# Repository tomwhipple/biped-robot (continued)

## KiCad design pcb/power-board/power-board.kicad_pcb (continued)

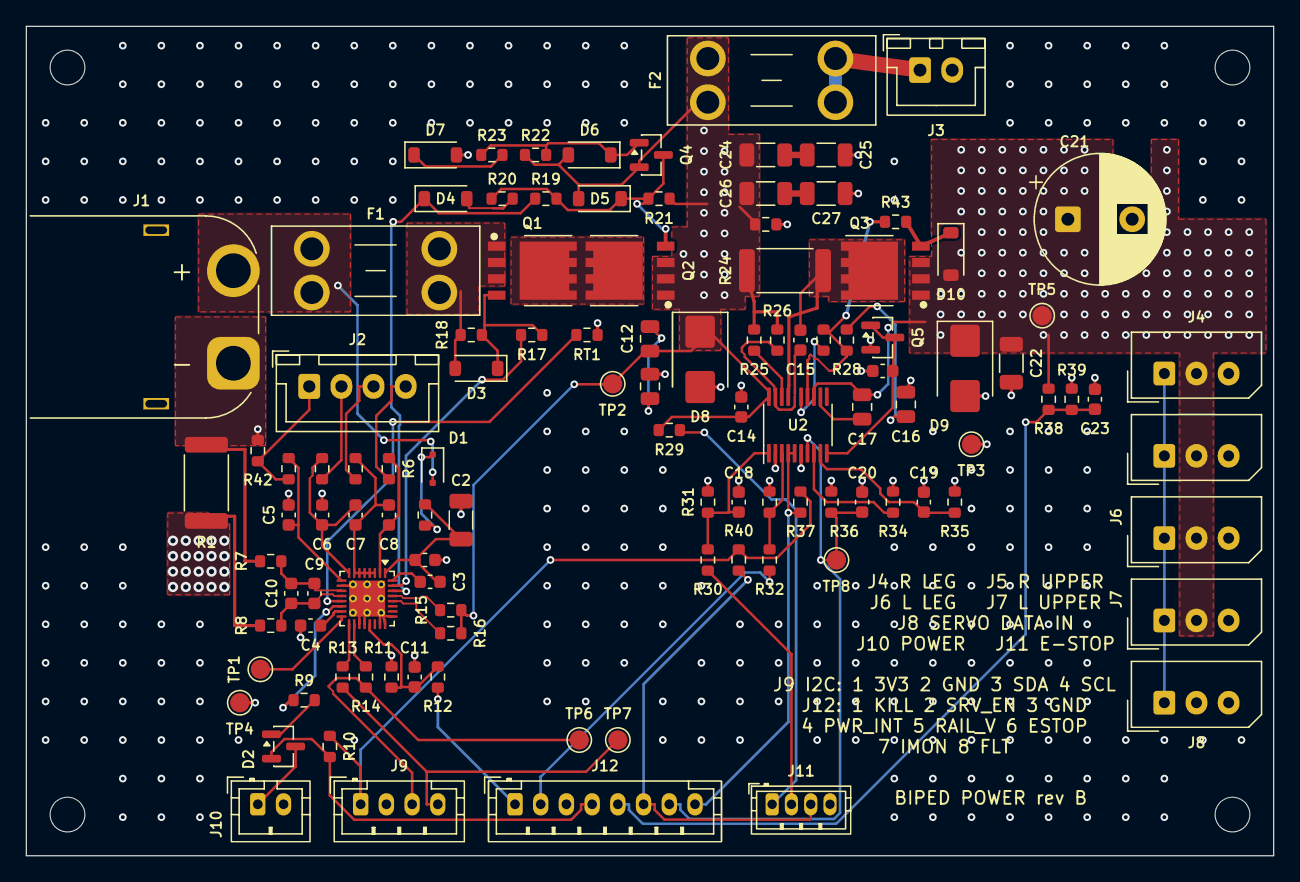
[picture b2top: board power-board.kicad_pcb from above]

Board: 4 copper layers, 97.0 x 64.5 mm, 115 parts (0 on the bottom side), 68 nets.

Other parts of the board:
H1, H2, H3, H4: M2.5; MountingHole_2.7mm_M2.5

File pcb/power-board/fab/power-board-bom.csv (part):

"Refs","Value","Footprint","MPN","Datasheet","Qty"
"C1","100p 50V","Capacitor_SMD:C_0603_1608Metric","Yageo CC0603JRNPO9BN101","https://yageogroup.com/download/specsheet/CC0603JRNPO9BN101","1"
"C2","2.2u 50V","Capacitor_SMD:C_1206_3216Metric","KEMET C1206C225K5RACTU","https://content.kemet.com/datasheets/KEM_C1002_X7R_SMD.pdf","1"
"C3","470n 25V","Capacitor_SMD:C_0603_1608Metric","Yageo CC0603KRX7R8BB474","https://yageogroup.com/content/datasheet/asset/file/UPY-GPHC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","1"
"C4","2.2u 10V","Capacitor_SMD:C_0603_1608Metric","Yageo CC0603KRX7R6BB225","https://yageogroup.com/content/datasheet/asset/file/UPY-GPHC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","1"
"C5-C8","100n 25V","Capacitor_SMD:C_0603_1608Metric","Yageo CC0603KRX7R9BB104","https://yageogroup.com/content/datasheet/asset/file/UPY-GPHC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","4"
"C9,C23","100n","Capacitor_SMD:C_0603_1608Metric","Yageo CC0603KRX7R9BB104","https://yageogroup.com/content/datasheet/asset/file/UPY-GPHC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","2"
"C10","100p","Capacitor_SMD:C_0603_1608Metric","Yageo CC0603JRNPO9BN101","https://yageogroup.com/download/specsheet/CC0603JRNPO9BN101","1"
"C11,C18,C20","10n","Capacitor_SMD:C_0603_1608Metric","Yageo CC0603KRX7R9BB103","https://yageogroup.com/content/datasheet/asset/file/UPY-GPHC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","3"
"C12,C13","100n 50V","Capacitor_SMD:C_0805_2012Metric","Yageo CC0805KRX7R9BB104","https://yageogroup.com/content/datasheet/asset/file/UPY-GPHC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","2"
"C14","100n 50V","Capacitor_SMD:C_0603_1608Metric","Yageo CC0603KRX7R9BB104","https://yageogroup.com/content/datasheet/asset/file/UPY-GPHC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","1"
"C15","1n","Capacitor_SMD:C_0603_1608Metric","Yageo CC0603JRNPO9BN102","https://yageogroup.com/download/specsheet/CC0603JRNPO9BN101","1"
"C16","330n 50V","Capacitor_SMD:C_0805_2012Metric","Samsung CL21B334KBFNNNE","https://product.samsungsem.com/mlcc/CL21B334KBFNNN.do","1"
"C17","4.7u 25V","Capacitor_SMD:C_0805_2012Metric","Samsung CL21B475KAFNNNE","https://product.samsungsem.com/mlcc/CL21B334KBFNNN.do","1"
"C19","680n 16V","Capacitor_SMD:C_0603_1608Metric","Yageo CC0603KRX7R7BB684","https://yageogroup.com/content/datasheet/asset/file/UPY-GPHC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","1"
"C21","1000u 25V","Capacitor_THT:CP_Radial_D10.0mm_P5.00mm","Panasonic EEU-FR1E102","https://industrial.panasonic.com/cdbs/www-data/pdf/RDF0000/A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","1"
"C22","10u 25V","Capacitor_SMD:C_1206_3216Metric","Samsung CL31B106KLHNNNE","https://mm.digikey.com/Volume0/opasdata/d220001/medias/docus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","1"
"D1","PMEG4002EJ","Diode_SMD:D_SOD-323F","Nexperia PMEG4002EJ-QX","https://assets.nexperia.com/documents/data-sheet/PMEG4002EJ-Q.pdf","1"
"D2","BAT54C","Package_TO_SOT_SMD:SOT-23","Diotec BAT54C","https://diotec.com/request/datasheet/bat54.pdf","1"
"D3,D5,D6","16V","Diode_SMD:D_SOD-123","Diodes MMSZ5246B-7-F","https://www.diodes.com/assets/Datasheets/ds18010.pdf","3"
"D4,D7","1N4148W","Diode_SMD:D_SOD-123","Diodes 1N4148W-7-F","https://www.diodes.com/assets/Datasheets/BAV16W_1N4148W.pdf","2"
"D8,D9","SMBJ15A","Diode_SMD:D_SMB","Bourns SMBJ15A","https://www.bourns.com/docs/Product-Datasheets/SMBJ.pdf","2"
"F1","15A","Fuse:Fuseholder_Blade_Mini_Keystone_3568","Keystone 3568 + Littelfuse 0297015.WXNV","https://www.keyelco.com/userAssets/file/K75p48.pdf","1"
"F2","3A","Fuse:Fuseholder_Blade_Mini_Keystone_3568","Keystone 3568 + Littelfuse 0297003.WXNV","https://www.keyelco.com/userAssets/file/K75p48.pdf","1"
"J1","XT60 pack","power-board:AMASS_XT60PW-M_1x02_P7.20mm_Horizontal_EdgeMount","Amass XT60PW-M","https://www.china-amass.com","1"
"J2","Balance 3S","Connector_JST:JST_XH_B4B-XH-A_1x04_P2.50mm_Vertical","JST B4B-XH-A","https://www.jst-mfg.com/product/pdf/eng/eXH.pdf","1"
"J3","LOGIC OUT","Connector_JST:JST_XH_B2B-XH-A_1x02_P2.50mm_Vertical","JST B2B-XH-A","https://www.jst-mfg.com/product/pdf/eng/eXH.pdf","1"
"J4","Servo R leg","Connector_Molex:Molex_SPOX_5267-03A_1x03_P2.50mm_Vertical","Molex 22-03-5035","https://www.molex.com/en-us/products/part-detail/22035035","1"
"J5","Servo R upper","Connector_Molex:Molex_SPOX_5267-03A_1x03_P2.50mm_Vertical","Molex 22-03-5035","https://www.molex.com/en-us/products/part-detail/22035035","1"
"J6","Servo L leg","Connector_Molex:Molex_SPOX_5267-03A_1x03_P2.50mm_Vertical","Molex 22-03-5035","https://www.molex.com/en-us/products/part-detail/22035035","1"
"J7","Servo L upper","Connector_Molex:Molex_SPOX_5267-03A_1x03_P2.50mm_Vertical","Molex 22-03-5035","https://www.molex.com/en-us/products/part-detail/22035035","1"
"J8","Data from H5","Connector_Molex:Molex_SPOX_5267-03A_1x03_P2.50mm_Vertical","Molex 22-03-5035","https://www.molex.com/en-us/products/part-detail/22035035","1"
"J9","I2C (to P1)","Connector_JST:JST_PH_B4B-PH-K_1x04_P2.00mm_Vertical","JST B4B-PH-K-S","https://www.jst-mfg.com/product/pdf/eng/ePH.pdf","1"
"J10","POWER button","Connector_JST:JST_PH_B2B-PH-K_1x02_P2.00mm_Vertical","JST B2B-PH-K-S","https://www.jst-mfg.com/product/pdf/eng/ePH.pdf","1"
"J11","E-STOP button","Connector_JST:JST_PH_B4B-PH-K_1x04_P2.00mm_Vertical","JST B4B-PH-K-S","https://www.jst-mfg.com/product/pdf/eng/ePH.pdf","1"
"J12","Control (ESP32)","Connector_JST:JST_PH_B8B-PH-K_1x08_P2.00mm_Vertical","JST B8B-PH-K-S","https://www.jst-mfg.com/product/pdf/eng/ePH.pdf","1"
"Q1-Q3","CSD17556Q5B","power-board:TI_SON-8_5x6mm_P1.27mm_CSD17556Q5B","CSD17556Q5B","https://www.ti.com/lit/ds/symlink/csd17556q5b.pdf","3"
"Q4","2N7002","Package_TO_SOT_SMD:SOT-23","Vishay 2N7002K-T1-GE3","https://www.vishay.com/docs/71333/2n7002k.pdf","1"
"Q5","MMBT3904","Package_TO_SOT_SMD:SOT-23","Diodes MMBT3904-7-F","https://www.diodes.com/assets/Datasheets/MMBT3904.pdf","1"
"R1","1m","Resistor_SMD:R_2512_6332Metric","Bourns CSS2H-2512R-1L00FE","https://www.bourns.com/docs/product-datasheets/css2h-2512.pdf","1"
"R2,R7,R8,R13,R14,R25","100","Resistor_SMD:R_0603_1608Metric","Yageo RC0603FR-07100RL","https://yageogroup.com/content/datasheet/asset/file/PYU-RC_G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","6"
"R3-R6","20","Resistor_SMD:R_0603_1608Metric","Yageo RC0603FR-0720RL","https://yageogroup.com/content/datasheet/asset/file/PYU-RC_G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","4"
"R9-R11,R15,R16,R19,R23,R37,R39,R40","10k","Resistor_SMD:R_0603_1608Metric","Yageo RC0603FR-0710KL","https://yageogroup.com/content/datasheet/asset/file/PYU-RC_G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","10"
"R12,R29,R32","1k","Resistor_SMD:R_0603_1608Metric","Yageo RC0603FR-071KL","https://yageogroup.com/content/datasheet/asset/file/PYU-RC_G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","3"
"R17","5.1k","Resistor_SMD:R_0603_1608Metric","Vishay CRCW06035K10FKEA","https://www.vishay.com/docs/20035/dcrcwe3.pdf","1"
"R18,R21,R22","10M","Resistor_SMD:R_0603_1608Metric","Yageo RC0603FR-0710ML","https://yageogroup.com/content/datasheet/asset/file/PYU-RC_G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","3"
"R20","4.7k","Resistor_SMD:R_0603_1608Metric","Yageo RC0603FR-074K7L","https://yageogroup.com/content/datasheet/asset/file/PYU-RC_G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","1"
"R24","2m","Resistor_SMD:R_2512_6332Metric","Bourns CSS2H-2512K-2L00F","https://www.bourns.com/docs/product-datasheets/css2h-2512.pdf","1"
"R26","4.64k","Resistor_SMD:R_0603_1608Metric","Yageo RC0603FR-074K64L","https://yageogroup.com/content/datasheet/asset/file/PYU-RC_G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","1"
"R27,R31,R33,R35","100k","Resistor_SMD:R_0603_1608Metric","Yageo RC0603FR-07100KL","https://yageogroup.com/content/datasheet/asset/file/PYU-RC_G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","4"
"R28","10","Resistor_SMD:R_0603_1608Metric","Yageo RC0603FR-0710RL","https://yageogroup.com/content/datasheet/asset/file/PYU-RC_G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","1"
"R30","560k","Resistor_SMD:R_0603_1608Metric","Yageo RC0603FR-07560KL","https://yageogroup.com/content/datasheet/asset/file/PYU-RC_G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","1"
"R34","30.1k","Resistor_SMD:R_0603_1608Metric","Yageo RC0603FR-0730K1L","https://yageogroup.com/content/datasheet/asset/file/PYU-RC_G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","1"
"R36","9.1k","Resistor_SMD:R_0603_1608Metric","Yageo RC0603FR-079K1L","https://yageogroup.com/content/datasheet/asset/file/PYU-RC_G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","1"
"R38","47k","Resistor_SMD:R_0603_1608Metric","Yageo RC0603FR-0747KL","https://yageogroup.com/content/datasheet/asset/file/PYU-RC_G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","1"
"RT1","10k NTC","Resistor_SMD:R_0603_1608Metric","Murata NCP18XH103F03RB","https://www.murata.com/-/media/webrenewal/products/thermisto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","1"
"TP1","ALERT","TestPoint:TestPoint_Pad_D1.5mm","","","1"
"TP2","PACK+","TestPoint:TestPoint_Pad_D1.5mm","","","1"
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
